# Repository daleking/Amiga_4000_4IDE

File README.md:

# Amiga 4000 4 way IDE Adaptor [UNTESTED]

Nothing fancy here.  Just your regular 4 way IDE adaptor for the Amiga 4000
that's been available on the interwebs for years.

## Prior Work

* [1997] [Amiga Info #1 | Mikael Fors](https://dmzarkivet.se/pager.cfm?issue=199701&page=36&ai=1) The Swedish artical that seems to have started it all.
* [1998] [Aminet 4IDE.lha](https://aminet.net/package/docs/hard/4IDE)
* [2003] [Roberto Ragusa](https://web.archive.org/web/20201101015014/https://members.xoom.virgilio.it/amigazette/numero_01/4ide.html) An Italian doc describing 4IDE
* [2016] [Fook42 @ a1k.org](https://www.a1k.org/forum/index.php?threads/57103/) The standard one, orderable at OSH Park
* [2019] [Gianluca Renzi](https://github.com/gianlucarenzi/4IDEAdapter) A neat
adapter for the A1200 referencing 4IDE.  I like the on-board LEDs!

Limitations of earlier work are that the LED is not active for the second channel
as it is disconnected.  This can be solved by connecting the /ACTIVE signal for
each channel through it's own blocking diode as the Amiga 4000 /IDE_LED signal
is already connected to +5V via 2.7k pull-up.

We™ won't© talk™ about® those™ other© guys™.

## BOM

* 3x 2x20 Pin Male IDC Box Connectors
* 4x Diodes e.g. BAT85 through hole or bodge some SMDs in there

* A short IDE cable to connect from your motherboard to the adapter.  There are
mounting holes to fit screw it somewhere out of the way or leave it flapping
(but isolate the rear of the PCB with some carboard so the solder points aren't
at risk of shorting anything out)

## Software

To get the second channel working you will need some software like:
* [AtapicMagic](https://aminet.net/package/driver/media/AtapiMagic)
* [IDEfix97](http://aminet.net/package/driver/media/IDEfix97.lha)

## Testing

| OS            | Software      | State    |
| ------------- |:-------------:|----------|
| 2.x           | IDEfix        | UNTESTED |
| 2.x           | AtapiMagic    | UNTESTED |
| 3.1           | IDEfix        | UNTESTED |
| 3.1           | AtapiMagic    | UNTESTED |
| 3.9           | IDEfix        | UNTESTED |
| 3.9           | AtapiMagic    | UNTESTED |
| 3.1.x/3.2.x   | IDEfix        | N/A      |
| 3.1.x/3.2.x   | AtapiMagic    | UNTESTED |

## LICENSE

This work is licensed as CC BY-NC-SA 4.0 so that means no commercial use but
feel free to sell a few extras on eBay for a reasonable (less than the other
guys™) price.

A shareable PCBWay project will be available if you'd like to support me a
little with future prototyping costs.

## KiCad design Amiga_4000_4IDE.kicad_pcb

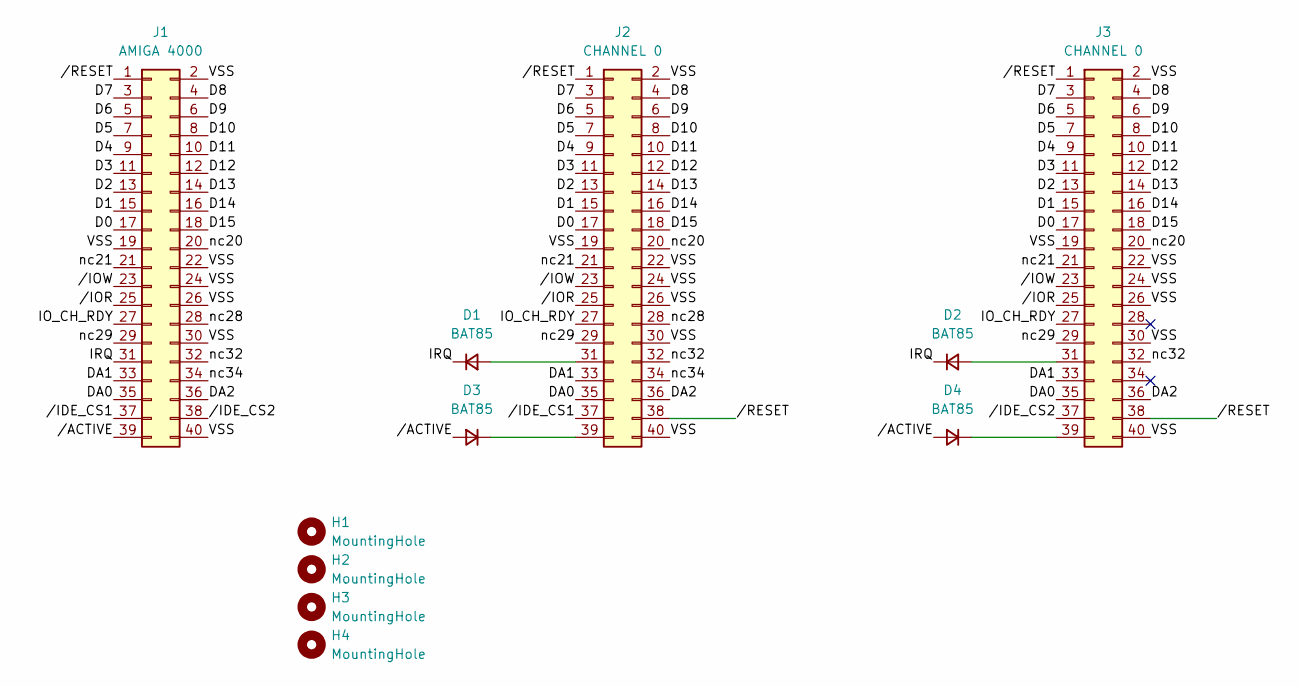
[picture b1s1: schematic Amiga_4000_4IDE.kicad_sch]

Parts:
D1, D2, D3, D4: BAT85; D_T-1_P5.08mm_Horizontal
H1, H2, H3, H4: MountingHole; MountingHole_3.2mm_M3
J1: AMIGA 4000; IDC-Header_2x20_P2.54mm_Vertical
J2, J3: CHANNEL 0; IDC-Header_2x20_P2.54mm_Vertical

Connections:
/D0: J1.17, J2.17, J3.17
/D1: J1.15, J2.15, J3.15
/D2: J1.13, J2.13, J3.13
/D3: J1.11, J2.11, J3.11
/D4: J1.9, J2.9, J3.9
/D5: J1.7, J2.7, J3.7
/D6: J1.5, J2.5, J3.5
/D7: J1.3, J2.3, J3.3
/D8: J1.4, J2.4, J3.4
/D9: J1.6, J2.6, J3.6
/D10: J1.8, J2.8, J3.8
/D11: J1.10, J2.10, J3.10
/D12: J1.12, J2.12, J3.12
/D13: J1.14, J2.14, J3.14
/D14: J1.16, J2.16, J3.16
/D15: J1.18, J2.18, J3.18
/DA0: J1.35, J2.35, J3.35
/DA1: J1.33, J2.33, J3.33
/DA2: J1.36, J2.36, J3.36
/IO_CH_RDY: J1.27, J2.27, J3.27
/IRQ: D1.1 (K), D2.1 (K), J1.31
/VSS: J1.2, J1.19, J1.22, J1.24, J1.26, J1.30, J1.40, J2.2, J2.19, J2.22, J2.24, J2.26, J2.30, J2.40, J3.2, J3.19, J3.22, J3.24, J3.26, J3.30, J3.40
/nc20: J1.20, J2.20, J3.20
/nc21: J1.21, J2.21, J3.21
/nc28: J1.28, J2.28
/nc29: J1.29, J2.29, J3.29
/nc32: J1.32, J2.32, J3.32
/nc34: J1.34, J2.34
//ACTIVE: D3.2 (A), D4.2 (A), J1.39
//IDE_CS1: J1.37, J2.37
//IDE_CS2: J1.38, J3.37
//IOR: J1.25, J2.25, J3.25
//IOW: J1.23, J2.23, J3.23
//RESET: J1.1, J2.1, J2.38, J3.1, J3.38
unnamed: D1.2 (A), J2.31
unnamed: D2.2 (A), J3.31
unnamed: D3.1 (K), J2.39
unnamed: D4.1 (K), J3.39

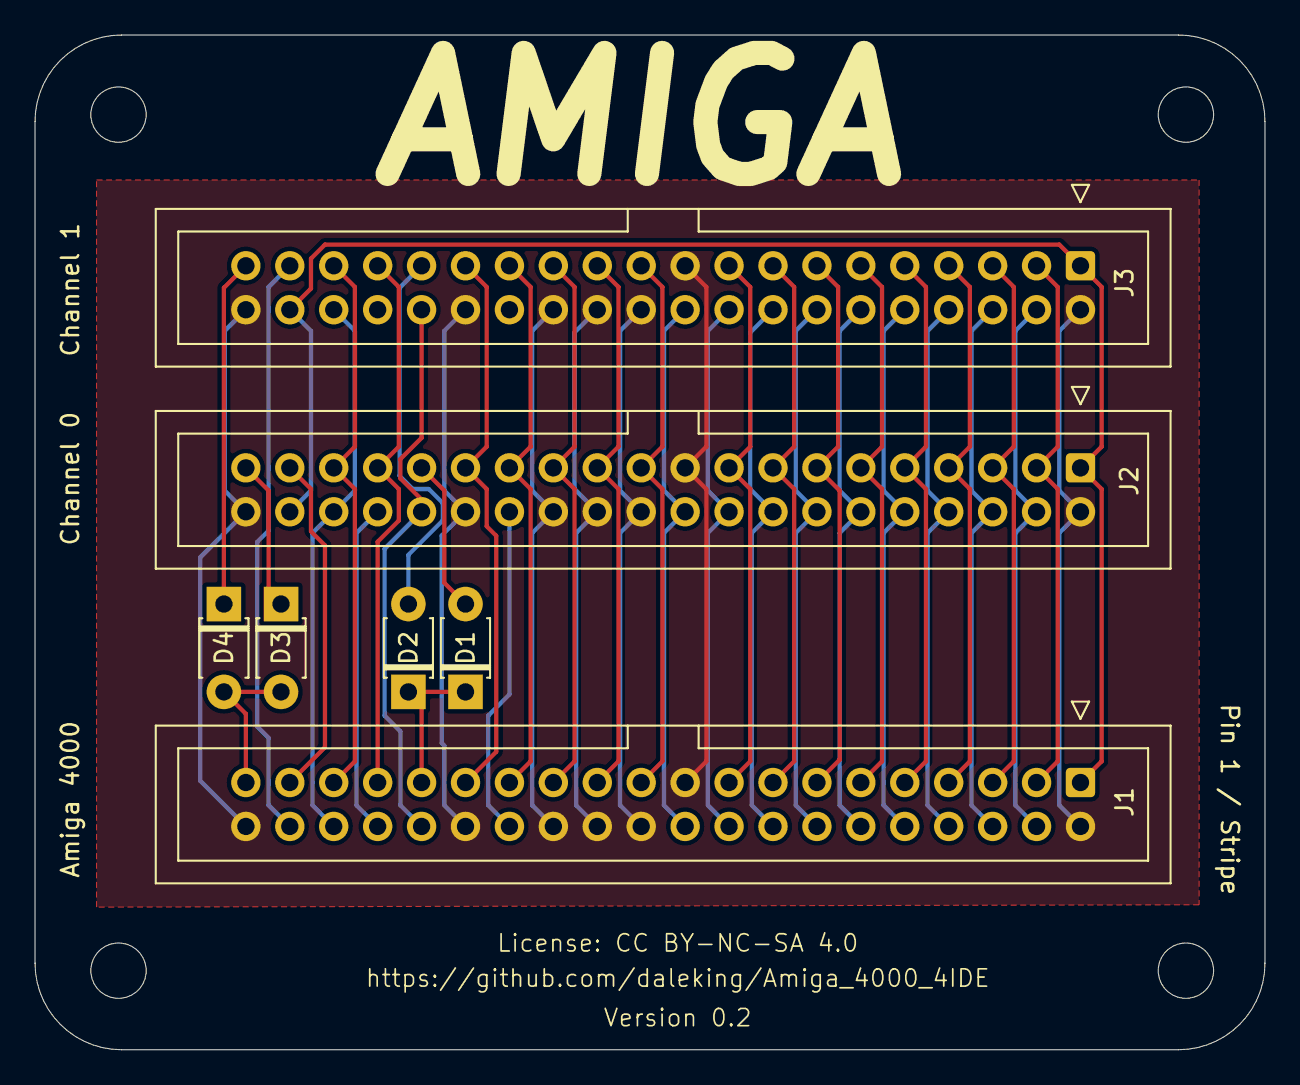
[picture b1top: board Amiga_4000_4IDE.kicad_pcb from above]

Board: 2 copper layers, 71.1 x 58.7 mm, 11 parts (0 on the bottom side), 38 nets.

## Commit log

2024-08-31 Initial Release
2024-09-28 Connect D7 (oops) and relayout PCB

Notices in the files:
Amiga_4000_4IDE.kicad_pcb:
License: CC BY-NC-SA 4.0
